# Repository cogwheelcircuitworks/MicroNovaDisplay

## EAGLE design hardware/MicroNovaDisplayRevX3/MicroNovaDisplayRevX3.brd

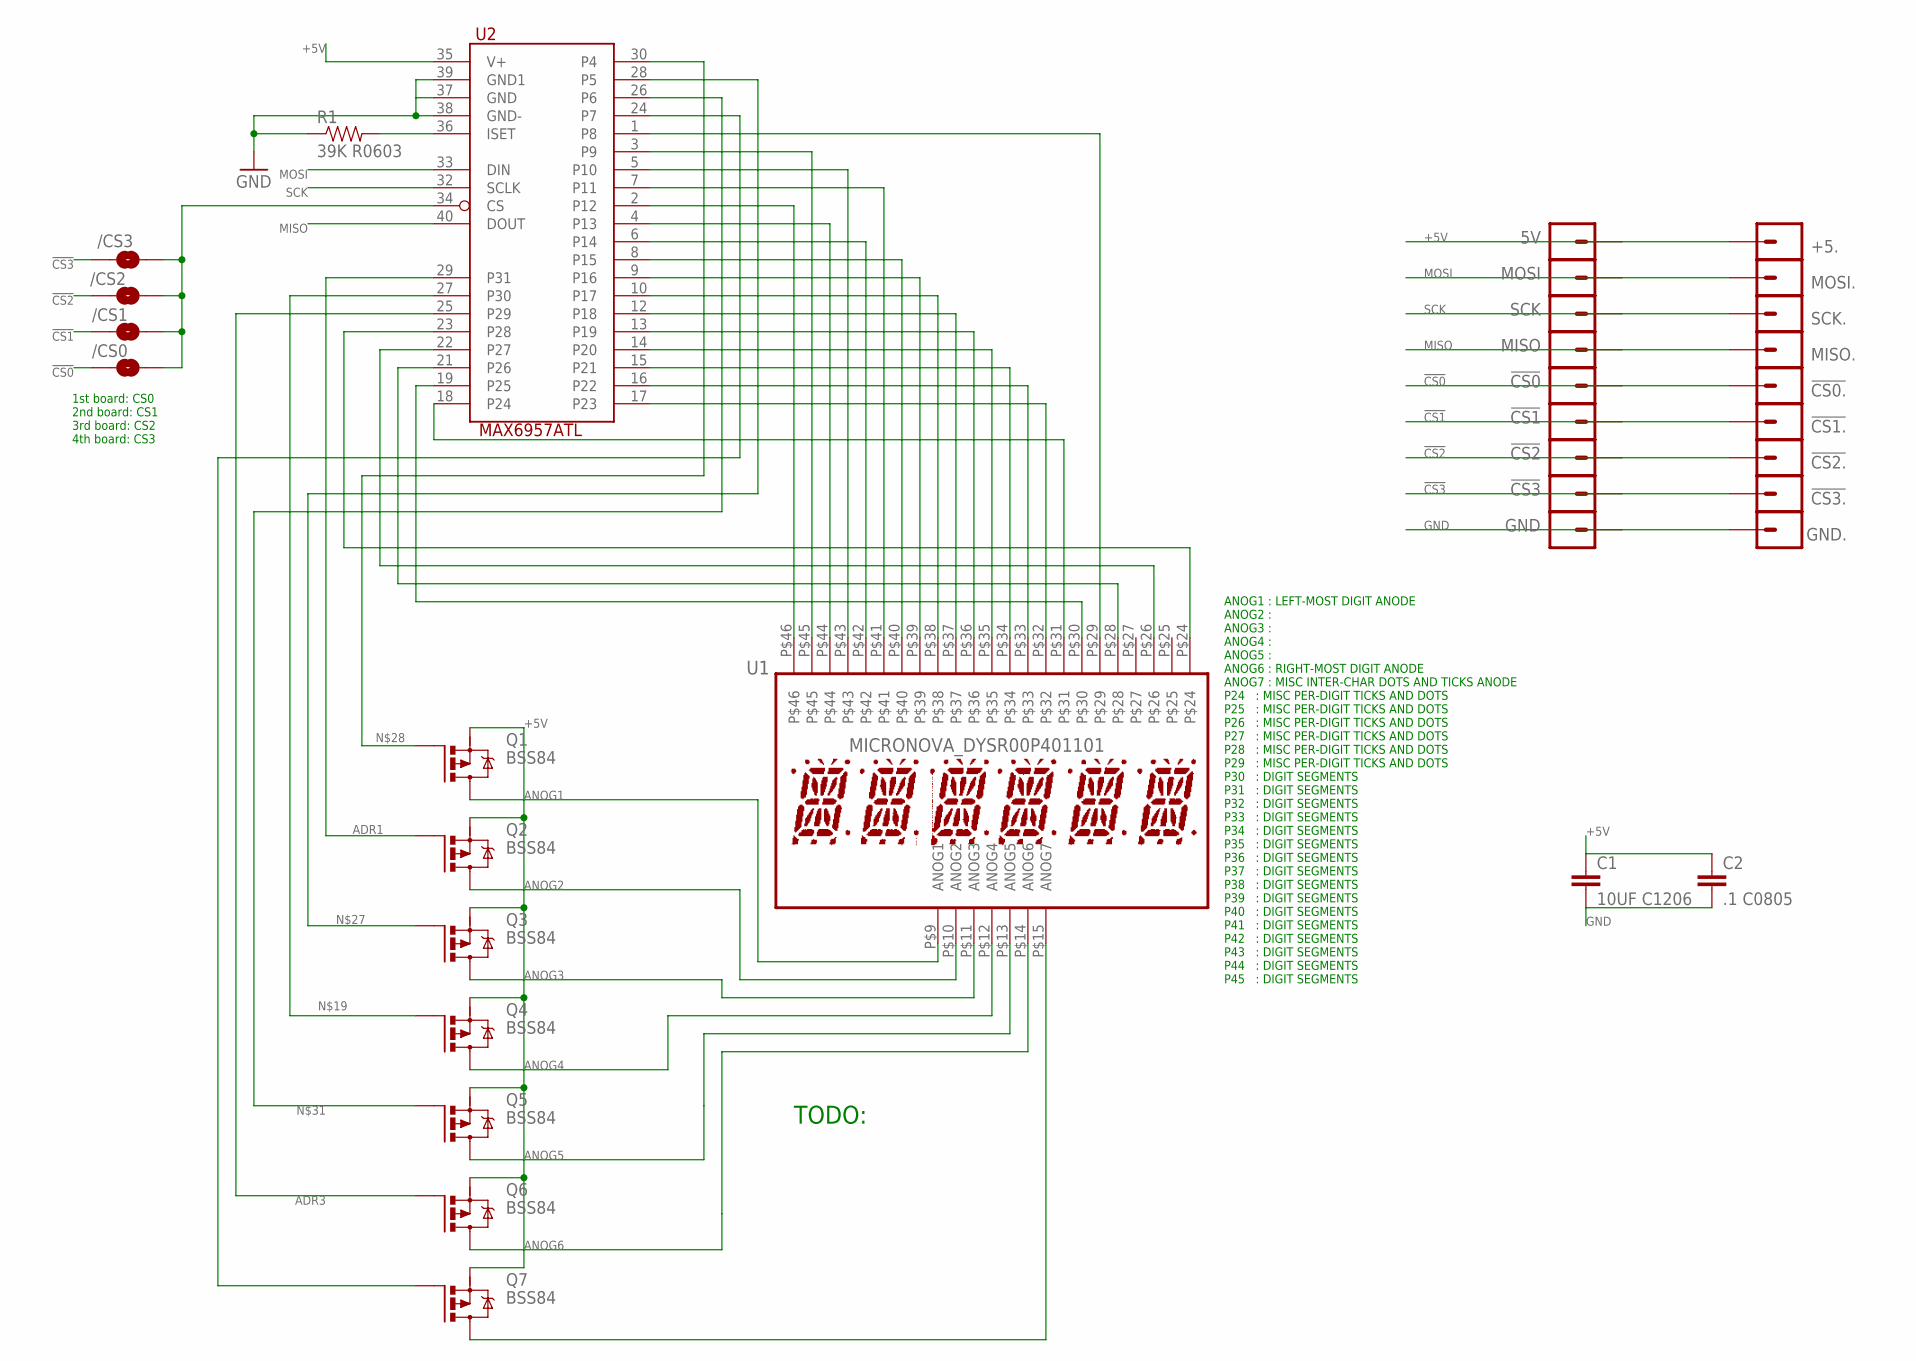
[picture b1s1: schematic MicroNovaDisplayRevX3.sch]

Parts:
5V: M01; 1X01_SMT_2MM
!CS0, !CS0., !CS1, !CS1., !CS2, !CS2., !CS3, !CS3.: M01; 1X01_SMT_2MM
+5.: M01; 1X01_SMT_2MM
/CS0, /CS1, /CS2, /CS3: JUMPER-PAD-2-NOYES_SILK; PAD-JUMPER-2-NO_YES_SILK
C1: 10UF C1206; 1206
C2: .1 C0805; 0805
GND, GND.: M01; 1X01_SMT_2MM
MISO, MISO.: M01; 1X01_SMT_2MM
MOSI, MOSI.: M01; 1X01_SMT_2MM
Q1, Q2, Q3, Q4, Q5, Q6, Q7: BSS84; SOT23-3
R1: 39K R0603; 0603
SCK, SCK.: M01; 1X01_SMT_2MM
U1: MICRONOVA_DYSR00P401101; ALPHANUMERIC
U2: MAX6957ATL; TQFP40

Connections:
!CS0: !CS0.P$1, !CS0..P$1, /CS0.1
!CS1: !CS1.P$1, !CS1..P$1, /CS1.1
!CS2: !CS2.P$1, !CS2..P$1, /CS2.1
!CS3: !CS3.P$1, !CS3..P$1, /CS3.1
+5V: 5V.P$1, +5..P$1, C1.1, C2.1, Q1.2 (1S), Q2.2 (1S), Q3.2 (1S), Q4.2 (1S), Q5.2 (1S), Q6.2 (1S), Q7.2 (1S), U2.35 (V+)
ADR1: Q2.1 (2G), U2.29 (P31)
ADR3: Q6.1 (2G), U2.25 (P29)
ADR4: Q7.1 (2G), U2.24 (P7)
ADR5: U1.P$30, U2.19 (P25)
ADR6: U1.P$28, U2.21 (P26)
ANOG1: Q1.3 (3D), U1.P$9 (ANOG1)
ANOG2: Q2.3 (3D), U1.P$10 (ANOG2)
ANOG3: Q3.3 (3D), U1.P$11 (ANOG3)
ANOG4: Q4.3 (3D), U1.P$12 (ANOG4)
ANOG5: Q5.3 (3D), U1.P$13 (ANOG5)
ANOG6: Q6.3 (3D), U1.P$14 (ANOG6)
GND: C1.2, C2.2, GND.P$1, GND..P$1, R1.1, U2.37 (GND), U2.38 (GND-), U2.39 (GND1)
MISO: MISO.P$1, MISO..P$1, U2.40 (DOUT)
MOSI: MOSI.P$1, MOSI..P$1, U2.33 (DIN)
unnamed: U1.P$31, U2.18 (P24)
unnamed: U1.P$32, U2.17 (P23)
unnamed: U1.P$33, U2.16 (P22)
unnamed: U1.P$34, U2.15 (P21)
unnamed: U1.P$35, U2.14 (P20)
unnamed: U1.P$36, U2.13 (P19)
unnamed: U1.P$37, U2.12 (P18)
unnamed: U1.P$38, U2.10 (P17)
unnamed: U1.P$39, U2.9 (P16)
unnamed: U1.P$40, U2.8 (P15)
unnamed: U1.P$41, U2.7 (P11)
unnamed: U1.P$42, U2.6 (P14)
unnamed: R1.2, U2.36 (ISET)
unnamed: U1.P$43, U2.5 (P10)
unnamed: U1.P$44, U2.4 (P13)
unnamed: U1.P$45, U2.3 (P9)
unnamed: U1.P$46, U2.2 (P12)
unnamed: U1.P$29, U2.1 (P8)
unnamed: Q4.1 (2G), U2.27 (P30)
unnamed: /CS0.2, /CS1.2, /CS2.2, /CS3.2, U2.34 (CS)
unnamed: U1.P$26, U2.22 (P27)
unnamed: U1.P$24, U2.23 (P28)
unnamed: Q7.3 (3D), U1.P$15 (ANOG7)
unnamed: Q3.1 (2G), U2.28 (P5)
unnamed: Q1.1 (2G), U2.30 (P4)
unnamed: Q5.1 (2G), U2.26 (P6)
SCK: SCK.P$1, SCK..P$1, U2.32 (SCLK)

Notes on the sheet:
ANOG1 : LEFT-MOST DIGIT ANODE ANOG2 : ANOG3 : ANOG4 : ANOG5 : ANOG6 : RIGHT-MOST DIGIT ANODE ANOG7 : MISC INTER-CHAR DOTS AND TICKS ANODE P24 : MISC PER-DIGIT TICKS AND DOTS P25 : MISC PER-DIGIT TICKS AND DOTS P26 : MISC PER-DIGIT TICKS AND DOTS P27 : MISC PER-DIGIT TICKS AND DOTS P28 : MISC PER-DI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
1st board: CS0 2nd board: CS1 3rd board: CS2 4th board: CS3
TODO:

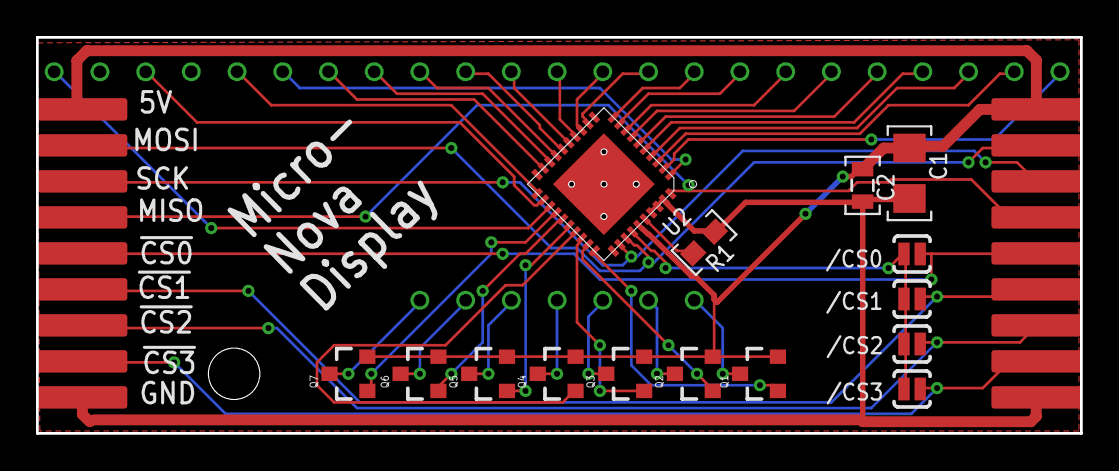
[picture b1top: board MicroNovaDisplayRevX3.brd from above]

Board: 2 copper layers, 58.0 x 22.0 mm, 35 parts (1 on the bottom side), 46 nets.

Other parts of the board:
JP4: MTGHOLE110MIL; HOLE112

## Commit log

2016-05-30 new file: software/libraries/MicroNovaDisplay/MAX6957.h new file: software/libraries/MicroNovaDisplay/MicroNovaDisplay.cpp new file: software/libraries/MicroNovaDisplay/MicroNovaDisplay.h new file: s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
2016-05-30 new file: hardware/MicroNovaDisplayRevX3/MicroNovaDisplay.gif new file: hardware/MicroNovaDisplayRevX3/MicroNovaDisplayRevX3.brd new file: hardware/MicroNovaDisplayRevX3/MicroNovaDisplayRevX3.lbr new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
2016-05-30 modified: README.md
2016-05-31 Touched up:
    hardware/MicroNovaDisplayRevX3/MicroNovaDisplayRevX3.sch
    Added pdfs
    hardware/MicroNovaDisplayRevX3/MicroNovaDisplayRevX3_bot.pdf
    hardware/MicroNovaDisplayRevX3/MicroNovaDisplayRevX3_sch.pdf
    hardware/MicroNovaDisplayRevX3/MicroNovaDisplayRevX3_top.pdf
2016-05-31 new file: hardware/MicroNovaDisplayRevX3/MicroNovaDisplayRevX3_bot.pdf new file: hardware/MicroNovaDisplayRevX3/MicroNovaDisplayRevX3_sch.pdf new file: hardware/MicroNovaDisplayRevX3/MicroNovaDisplay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
2016-06-01 modified: hardware/MicroNovaDisplayRevX3/MicroNovaDisplayRevX3_sch.pdf
